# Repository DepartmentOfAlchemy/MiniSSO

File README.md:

**MiniSSO**

The MiniSSO is a [FeatherWing](https://learn.adafruit.com/adafruit-feather/featherwings) designed for the [Feather](https://learn.adafruit.com/adafruit-feather) ecosystem create by [Adafruit](https://www.adafruit.com). It provides 1 optically isolated input and 2 solid state PWM outputs. The board is designed to be a haunted attraction prop control system. The input is for the prop trigger. And the outputs can drive 12V LED lights and 12V pneumatic solinoids or 12V relays.

**Pinout**
* Isolated input: D13 (Jumper alternative A3)
* PWM output 1: D12 (Jumper alternative A4)
* PWM output 2: D11 (Jumper alternative A5)

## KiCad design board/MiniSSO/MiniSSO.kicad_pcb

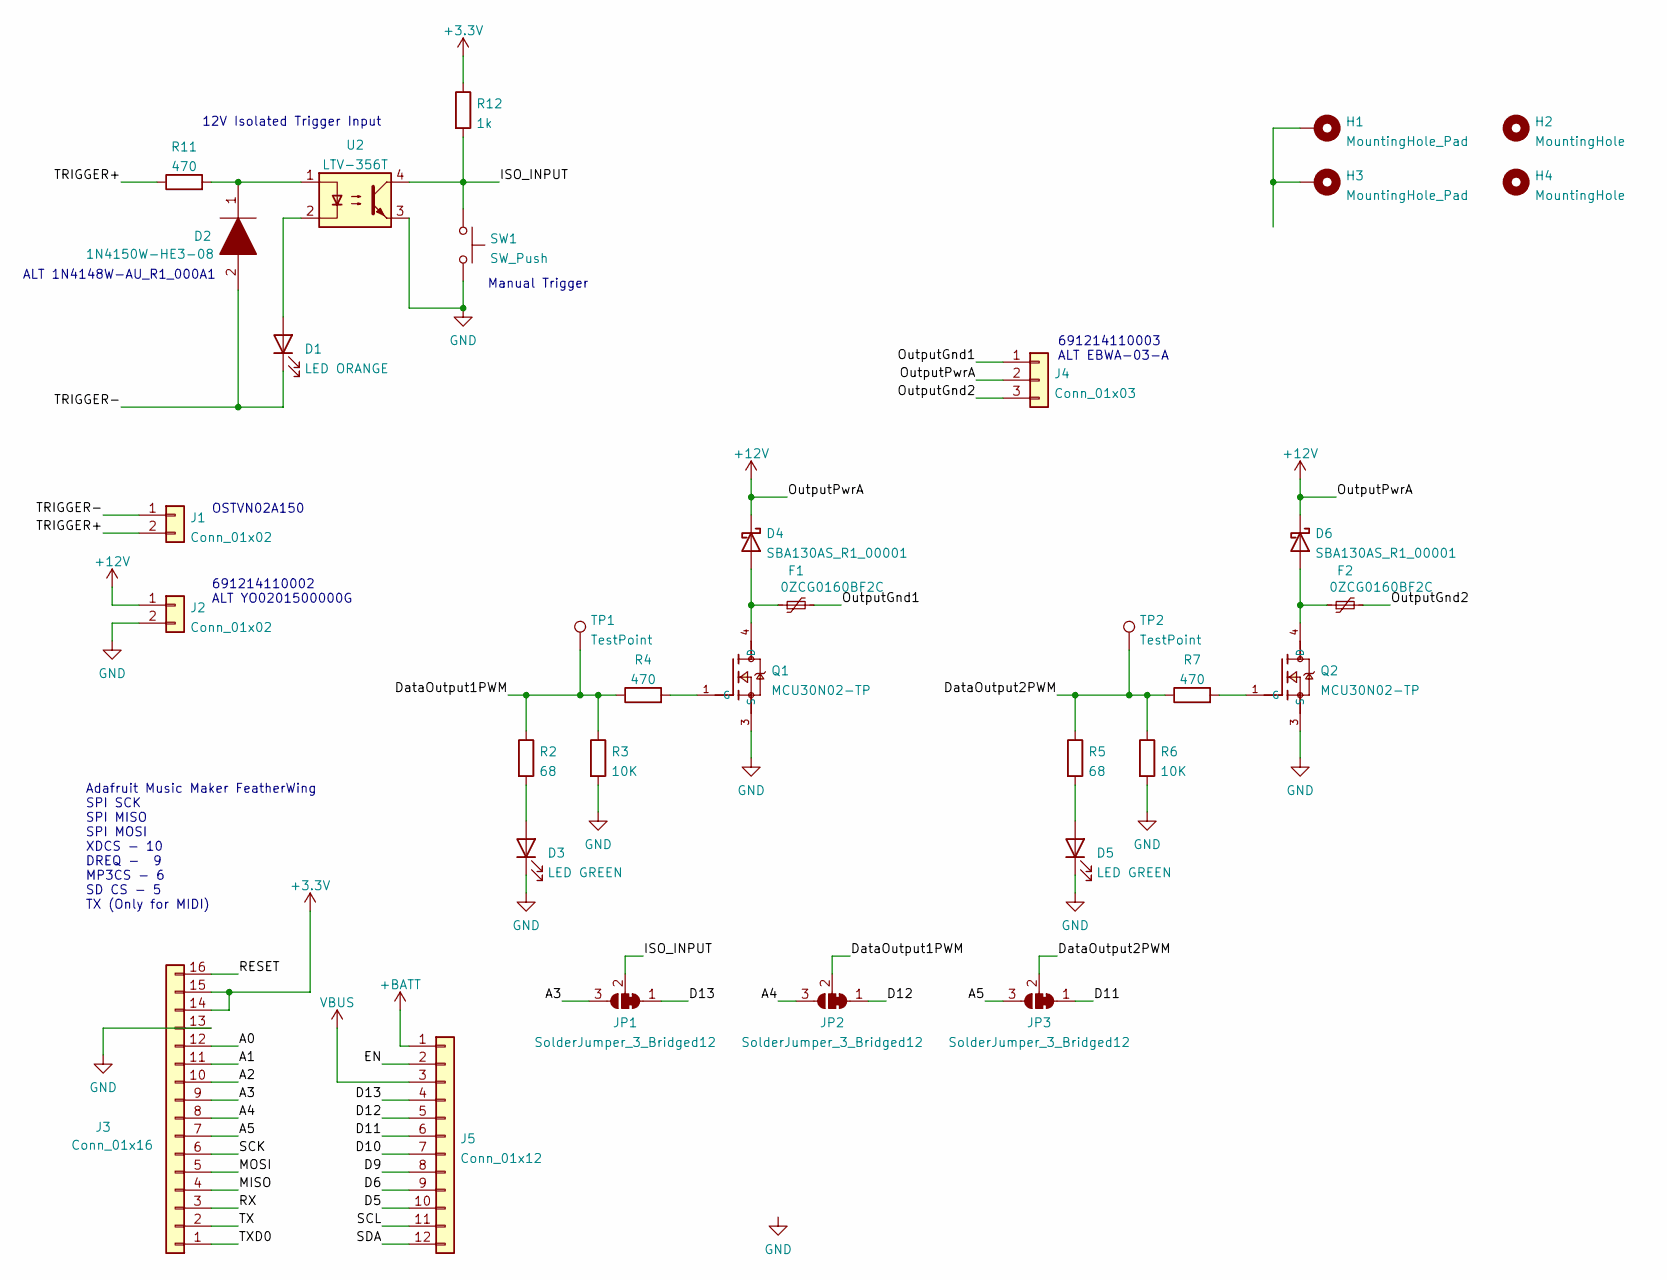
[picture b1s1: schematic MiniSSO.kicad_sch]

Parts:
D1: LED ORANGE; LED_0603_1608Metric
D2: 1N4150W-HE3-08; D_SOD-123; Manufacturer_Part_Number S1GTR
D3, D5: LED GREEN; LED_0603_1608Metric
D4, D6: SBA130AS_R1_00001; D_SOD-123
F1, F2: 0ZCG0160BF2C; Fuse_1812_4532Metric
H1, H3: MountingHole_Pad; MountingHole_2.7mm_M2.5_ISO14580_Pad
H2, H4: MountingHole; MountingHole_2.7mm_M2.5_ISO14580
J1: Conn_01x02; OSTVN02A150
J2: Conn_01x02; 691214110002
J3: Conn_01x16; PinHeaderPlain_1x16_P2.54mm_Vertical
J4: Conn_01x03; 691214110003
J5: Conn_01x12; PinHeaderPlain_1x12_P2.54mm_Vertical
JP1, JP2, JP3: SolderJumper_3_Bridged12; SolderJumper-3_P1.3mm_Bridged12_RoundedPad1.0x1.5mm
Q1, Q2: MCU30N02-TP; TO229P991X239-3N
R2, R5: 68; R_0603_1608Metric
R3, R6: 10K; R_0603_1608Metric
R4, R7, R11: 470; R_0603_1608Metric
R12: 1k; R_0603_1608Metric
SW1: SW_Push; SW_Push_1P1T_NO_CK_KMR2
TP1, TP2: TestPoint; TestPoint_Pad_D2.5mm
U2: LTV-356T; SO-4_4.4x3.6mm_P2.54mm

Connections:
+3V3: J3.14, J3.15, R12.1
+12V: D4.1 (K), D6.1 (K), J2.1, J4.2
+BATT: J5.1
/A0: J3.12
/A1: J3.11
/A2: J3.10
/A3: J3.9, JP1.3 (B)
/A4: J3.8, JP2.3 (B)
/A5: J3.7, JP3.3 (B)
/D5: J5.10
/D6: J5.9
/D9: J5.8
/D10: J5.7
/D11: J5.6, JP3.1 (A)
/D12: J5.5, JP2.1 (A)
/D13: J5.4, JP1.1 (A)
/DataOutput1PWM: JP2.2 (C), R2.1, R3.1, R4.1, TP1.1
/DataOutput2PWM: JP3.2 (C), R5.1, R6.1, R7.1, TP2.1
/EN: J5.2
/ISO_INPUT: JP1.2 (C), R12.2, SW1.1, U2.4
/MISO: J3.4
/MOSI: J3.5
/OutputGnd1: F1.2, J4.1
/OutputGnd2: F2.2, J4.3
/RESET: J3.16
/RX: J3.3
/SCK: J3.6
/SCL: J5.11
/SDA: J5.12
/TRIGGER+: J1.2, R11.1
/TRIGGER-: D1.1 (K), D2.2, J1.1
/TX: J3.2
/TXD0: J3.1
unnamed: D1.2 (A), U2.2
unnamed: D2.1, R11.2, U2.1
unnamed: D3.2 (A), R2.2
unnamed: D4.2 (A), F1.1, Q1.4 (D)
unnamed: D5.2 (A), R5.2
unnamed: D6.2 (A), F2.1, Q2.4 (D)
unnamed: Q1.1 (G), R4.2
unnamed: Q2.1 (G), R7.2
VBUS: J5.3

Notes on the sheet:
12V Isolated Trigger Input
691214110003 ALT EBWA-03-A
Manual Trigger
Adafruit Music Maker FeatherWing SPI SCK SPI MISO SPI MOSI XDCS - 10 DREQ - 9 MP3CS - 6 SD CS - 5 TX (Only for MIDI)
OSTVN02A150
691214110002 ALT YO0201500000G
ALT 1N4148W-AU_R1_000A1

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
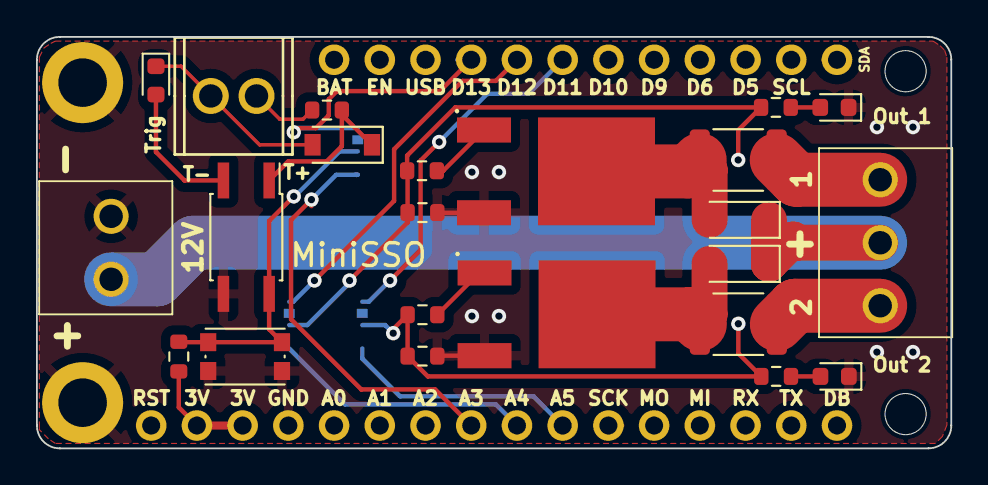
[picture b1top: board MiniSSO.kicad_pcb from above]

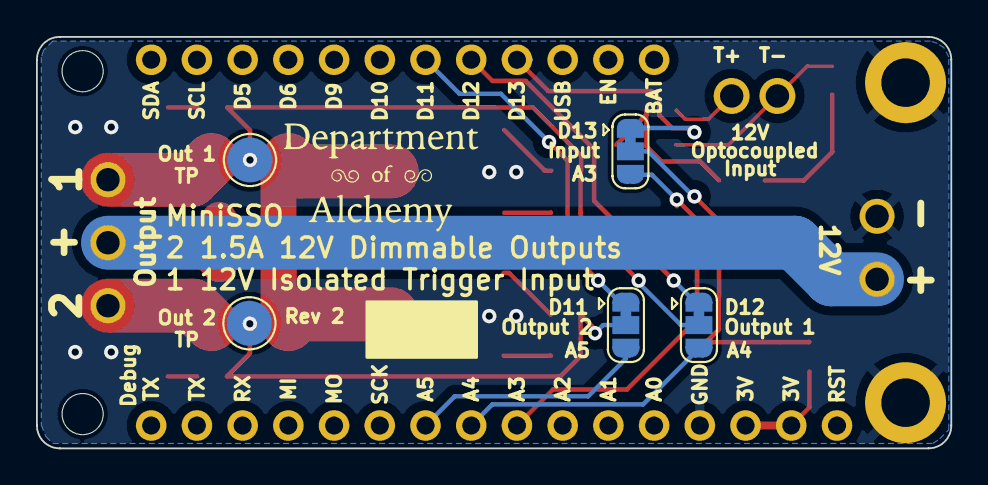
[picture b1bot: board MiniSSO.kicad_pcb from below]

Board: 2 copper layers, 50.8 x 22.9 mm, 34 parts (5 on the bottom side), 24 nets.

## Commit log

2022-04-11 First complete layout of board. Still need silkscreen documentation.
2022-04-17 Rev 1: Initial version of the board.
2022-04-17 Rev 1: PCB changed after final zone file and DRC before making gerbers.
2022-04-17 Rev 1: Save gerber output settings.
2022-04-17 Rev 1: Modified trace to solder bridge for input to provide larger ground plane around the solder bridge.
2023-06-13 Revision 2. First production board run.
2023-06-13 Added license.
2023-08-08 Update README.md
    Added initial basic information about the MiniSSO FeatherWing.
